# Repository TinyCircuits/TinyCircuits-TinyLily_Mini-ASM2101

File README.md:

# TinyCircuits TinyLily Mini Processor Board
# ASM2101 Rev4

Thhe design files are located under design_files/ for the TinyCircuits ASM2101 Rev 4 PCB.  This is a Tiny processor board (Circular 14mm diameter) that uses the same microcontroller (Atmel Atmega328P) as the Arduino LilyPad.

Format is in Cadsoft Eagle format - Eagle version 6.2 was used for the original design.

For more infomation on this, check out the product page at TinyCircuits.com: https://tinycircuits.com/collections/tinylily/products/tinylily-mini-processor

# License:

Design by TinyCircuits.
All design files are released under the Creative Commons Attribution Share-Alike 3.0 License, see the following link for details: http://creativecommons.org/licenses/by-sa/3.0

All text above must be included in any redistribution or derived design

This project uses designs and concepts developed as part of the Arduino project and the LilyPad project.  The TinyCircuits design files themselves (schematics, PCB and libraries) are not directly derived from these works' design files and have been created new, however the concepts and basic architecture behind the TinyDuino and TinyLily products are derived and we thank the hard work of the organizations below for their contributions to open-source hardware:
  
Original Arduino Uno Design by Team Arduino

LilyPad Arduino Design by Leah Buechley and Sparkfun Electronics

Please support the open-source hardware community

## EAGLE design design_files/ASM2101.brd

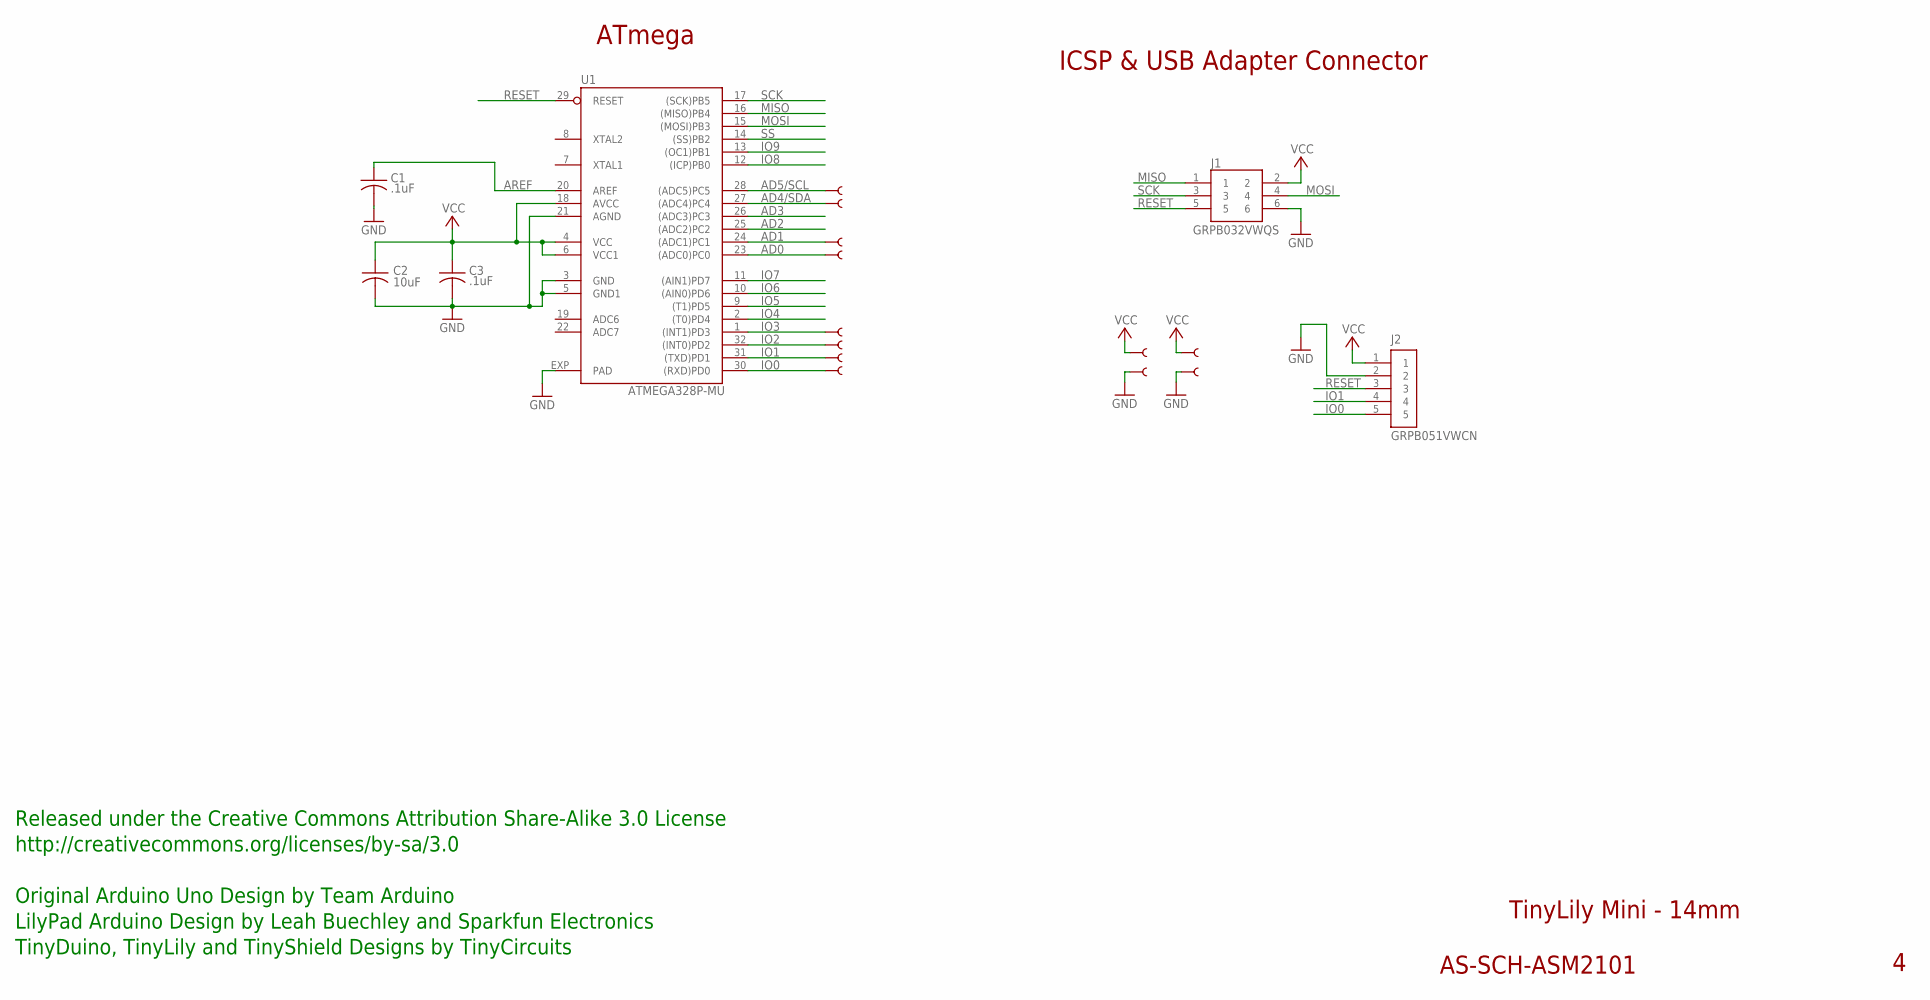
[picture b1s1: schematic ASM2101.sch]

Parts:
$1: SEWTAB; SEWTAP_TH
C1, C3: .1uF; C0402; PARTNO AS-ITM-00008
C2: 10uF; C0603; PARTNO AS-ITM-00002
J1: GRPB032VWQS; 2X3_.05"_SMT_HEADER
J2: GRPB051VWCN; 1X5_.05_RA_TH_HEADER
U1: ATMEGA328P-MU; ATMEL_QFN32; PARTNO AS-ITM-00013
U$1, U$2, U$3, U$4, U$5, U$7, U$8, U$9, U$10, U$11, U$12: SEWTAB; SEWTAP_TH

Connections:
AD0: U1.23 ((ADC0)PC0), U$4.1
AD1: U1.24 ((ADC1)PC1), U$3.1
AD2: U1.25 ((ADC2)PC2)
AD3: U1.26 ((ADC3)PC3)
AD4/SDA: U1.27 ((ADC4)PC4), U$2.1
AD5/SCL: U1.28 ((ADC5)PC5), U$1.1
AREF: C1.1, U1.20 (AREF)
GND: C1.2, C2.2, C3.2, J1.6, J2.2, U1.3 (GND), U1.5 (GND1), U1.21 (AGND), U1.EXP (PAD), U$11.1, U$12.1
IO0: J2.5, U1.30 ((RXD)PD0), U$10.1
IO1: J2.4, U1.31 ((TXD)PD1), U$9.1
IO2: $1.1, U1.32 ((INT0)PD2)
IO3: U1.1 ((INT1)PD3), U$5.1
IO4: U1.2 ((T0)PD4)
IO5: U1.9 ((T1)PD5)
IO6: U1.10 ((AIN0)PD6)
IO7: U1.11 ((AIN1)PD7)
IO8: U1.12 ((ICP)PB0)
IO9: U1.13 ((OC1)PB1)
MISO: J1.1, U1.16 ((MISO)PB4)
MOSI: J1.4, U1.15 ((MOSI)PB3)
RESET: J1.5, J2.3, U1.29 (RESET)
SCK: J1.3, U1.17 ((SCK)PB5)
SS: U1.14 ((SS)PB2)
VCC: C2.1, C3.1, J1.2, J2.1, U1.4 (VCC), U1.6 (VCC1), U1.18 (AVCC), U$7.1, U$8.1

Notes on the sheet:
ATmega
TinyLily Mini - 14mm
AS-SCH-ASM2101
Released under the Creative Commons Attribution Share-Alike 3.0 License
http://creativecommons.org/licenses/by-sa/3.0
Original Arduino Uno Design by Team Arduino
TinyDuino, TinyLily and TinyShield Designs by TinyCircuits
ICSP & USB Adapter Connector
LilyPad Arduino Design by Leah Buechley and Sparkfun Electronics

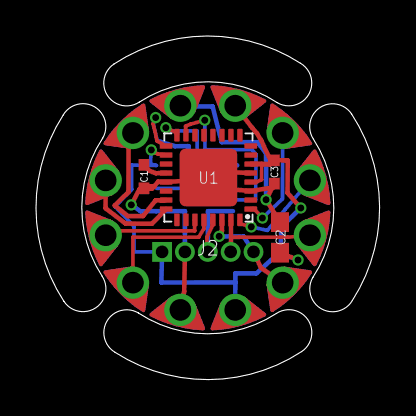
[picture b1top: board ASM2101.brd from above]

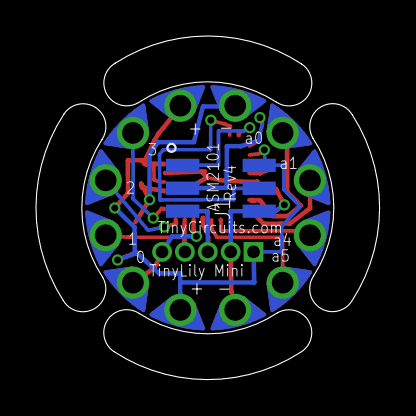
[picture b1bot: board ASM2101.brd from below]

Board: 2 copper layers, 19.1 x 19.1 mm, 19 parts (13 on the bottom side), 15 nets.

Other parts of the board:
U$6: DOCFIELD-TINYCIRCUITS-PCB

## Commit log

2013-06-30 Updated project link
2014-08-24 Updated Link
2016-02-02 Updated to Rev 3
2019-01-04 update format
2019-05-24 images
2019-05-28 color-friendly pinout
2019-05-28 pics
2019-05-28 crop
2019-08-01 SPI cy diagram
2020-02-13 image
2020-08-19 Add CAD data
